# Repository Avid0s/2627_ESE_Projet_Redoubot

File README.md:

# 2627_ESE_PROJET_REDOUBOT

[Diagramme draw.io](https://app.diagrams.net/#G1vOe_3MKJzJUBpPdtP-GZ-P4Yg8ShrS2W#%7B%22pageId%22%3A%22ODYEVYFFD_o6EEWGu_Kz%22%7D)

[PDF MPU 6050](https://docs.google.com/document/d/1O3AgjvM2_tZX7ABNkbS3lNtyRqeFLNvJ6qVK9URJxNs/edit?usp=drive_link)

[BOM commande composants](https://docs.google.com/spreadsheets/d/1_k0gg7k1Y5h9V0FLCA0YabgreAiMSMoDTZmiZd1OaFM/edit?usp=sharing)

| Composant | Référence | Lien | Quantité |
|-----------|-----------|------|----------|
| STM32 | CPU_DS_stm32g431rb | [Datasheet](https://github.com/Avid0s/2627_ESE_Projet_Redoubot/blob/main/Datasheet/CPU_DS_stm32g431rb.pdf) | x1 |
| Drivers moteur | DRV8833 | [Datasheet](https://github.com/Avid0s/2627_ESE_Projet_Redoubot/blob/main/Datasheet/Drivers_drv8833.pdf) | x1 |
| Moteurs | FIT0483 | [Datasheet](https://github.com/Avid0s/2627_ESE_Projet_Redoubot/blob/main/Datasheet/Datasheet_moteur_FIT0483.pdf) | x2|
| Gyroscope/accelerometre | MPU6050 | [Datasheet](https://github.com/Avid0s/2627_ESE_Projet_Redoubot/blob/main/Datasheet/Gyro_MPU-6000_DATASHEET.pdf) | x1 |
| Servomotor | SER0039 | [Datasheet](https://github.com/Avid0s/2627_ESE_Projet_Redoubot/blob/main/Datasheet/Servo_SER0039.pdf) | x2 |
| TOF sensor | VL53LL0X | [Datasheet](https://github.com/Avid0s/2627_ESE_Projet_Redoubot/blob/main/Datasheet/TOF_vl53l0x.pdf) [Breakout Board](https://github.com/lfiack/ENSEA_VL53L0CXV0DH-1)| x1 |
| Capteur de couleur | Adafruit APDS9960 | [Datasheet](https://github.com/Avid0s/2627_ESE_Projet_Redoubot/blob/main/Datasheet/Capteur_Couleur_9075d4adc221e10b04bda232a5ca3905.pdf) | x1 |
| BMS | BQ25896RTWR | [Datasheet](https://github.com/Avid0s/2627_ESE_Projet_Redoubot/blob/main/Datasheet/BMS_bq25896.pdf) | x1 |  
| Batterie Lithium | XX | Fournie par ENSEA | x1 |
| Fuel Gauge | BQ27220YZFR | [Datasheet](https://www.ti.com/lit/ds/symlink/bq27220.pdf?ts=1790240333206&ref_url=https%253A%252F%252Fwww.mouser.fr%252F) | x1 |
| Sonde de programation | Conn_ST_STDC14 | Fournie par ENSEA| x1 |
| Lecteur MicroSD | Module MP3 DFPlayer | XX | x1 |
| Module Bluetooth | BT Module HM10 | XX | x1 |

La facon dont l'implémentation de fonctionnalités sera faite sera la suivante:

1 branche = 1 fonctionalité

Les branches seront nommées JMA/nom_de_la_fonctionnalitée pour une branche fonctionnalité de J. Mansard par exemple

Aucun push ne sera fait directement sur le main, tout sera merge post peer review

Cette methodologie vise à éviter les merge conflicts et simplifier l'assemblage des différents modules

## TODO :
- Timeline des tests phase bringup (tests réussis, échoués etc)
- faire un organigramme de la partie software pour arrêter de coder en blind
- Créer schémas de programmation, style de ce qui a été fait en cours de RTOS (session4 p7)
- Créer chronogrammes pour machines à état avec tâches blocantes

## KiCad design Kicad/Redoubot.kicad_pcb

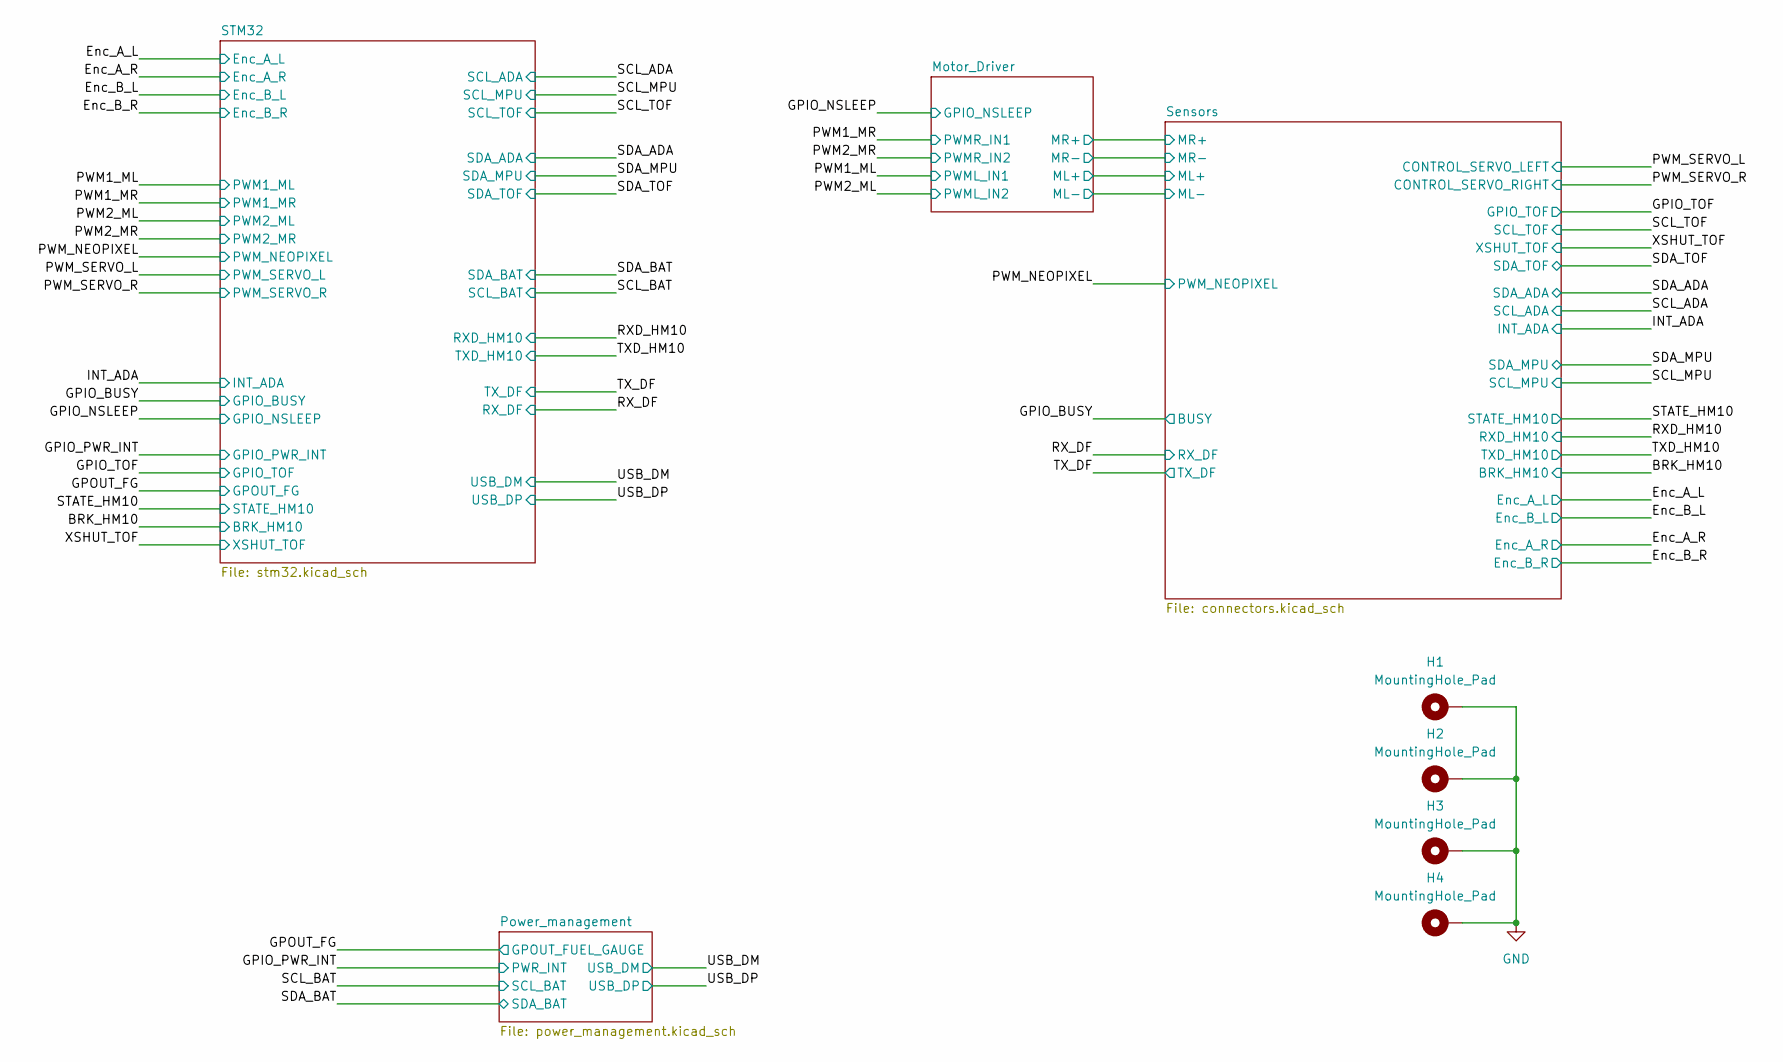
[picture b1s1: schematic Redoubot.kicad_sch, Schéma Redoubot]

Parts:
H1, H2, H3, H4: MountingHole_Pad; MountingHole_3.2mm_M3_ISO7380_Pad_TopBottom

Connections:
GND: H1.1 (1_1), H2.1 (1_1), H3.1 (1_1), H4.1 (1_1); also elsewhere on the board

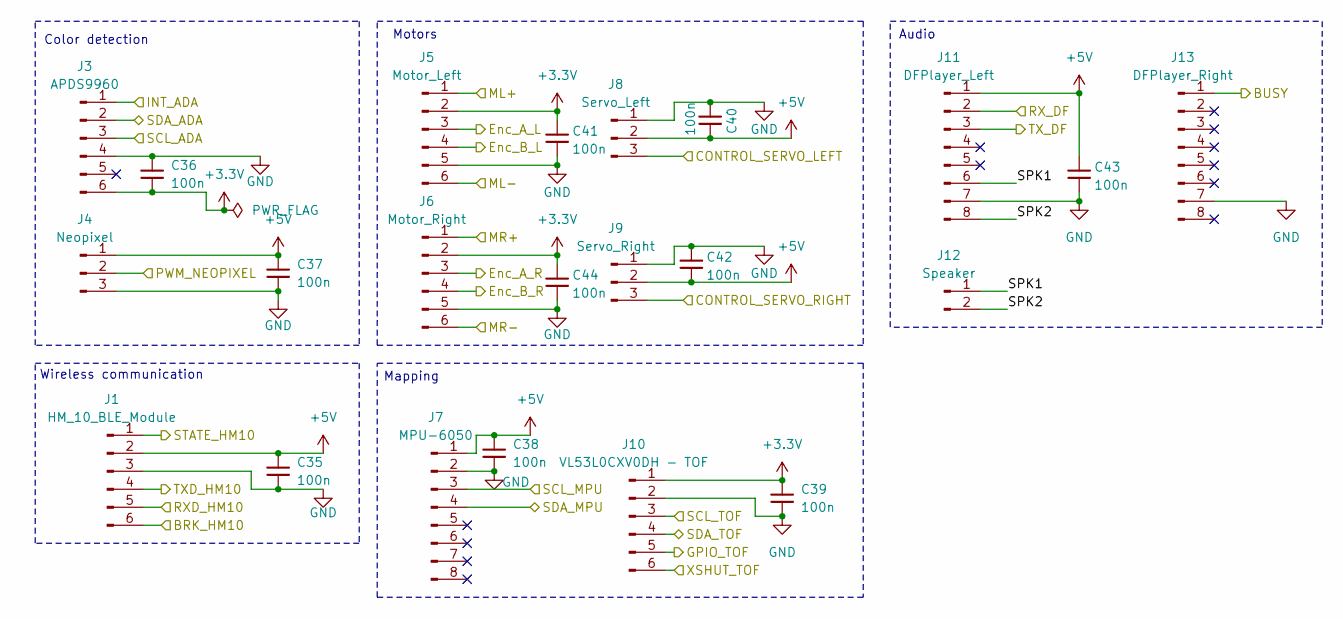
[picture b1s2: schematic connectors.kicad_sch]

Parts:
C35, C36, C37, C38, C39, C40, C41, C42, C43, C44: 100n; C_0402_1005Metric; JLCPCB Part # C1525
J1: HM_10_BLE_Module; JST_XH_B6B-XH-A_1x06_P2.50mm_Vertical
J3: APDS9960; JST_XH_B6B-XH-A_1x06_P2.50mm_Vertical
J4: Neopixel; JST_XH_B3B-XH-A_1x03_P2.50mm_Vertical
J5: Motor_Left; JST_XH_B6B-XH-A_1x06_P2.50mm_Vertical
J6: Motor_Right; JST_XH_B6B-XH-A_1x06_P2.50mm_Vertical
J7: MPU-6050; PinSocket_1x08_P2.54mm_Vertical; LCSC C24112
J8: Servo_Left; JST_XH_B3B-XH-A_1x03_P2.50mm_Vertical
J9: Servo_Right; JST_XH_B3B-XH-A_1x03_P2.50mm_Vertical
J10: VL53L0CXV0DH - TOF; JST_XH_B6B-XH-A_1x06_P2.50mm_Vertical; LCSC C91199
J11: DFPlayer_Left; PinSocket_1x08_P2.54mm_Vertical
J12: Speaker; JST_XH_B2B-XH-A_1x02_P2.50mm_Vertical
J13: DFPlayer_Right; PinSocket_1x08_P2.54mm_Vertical

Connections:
+3.3V: C36.2, C39.1, C41.1, C44.1, J3.6, J5.2, J6.2, J10.1; also elsewhere on the board
+5V: C35.1, C37.1, C38.1, C40.2, C42.2, C43.1, J1.2, J4.1, J7.1, J8.2, J9.2, J11.1; also elsewhere on the board
/BRK_HM10: J1.6; also elsewhere on the board
/Enc_A_L: J5.3; also elsewhere on the board
/Enc_A_R: J6.3; also elsewhere on the board
/Enc_B_L: J5.4; also elsewhere on the board
/Enc_B_R: J6.4; also elsewhere on the board
/GPIO_BUSY: J13.1; also elsewhere on the board
/GPIO_TOF: J10.5; also elsewhere on the board
/INT_ADA: J3.1; also elsewhere on the board
/Motor_Driver/ML+: J5.1; also elsewhere on the board
/Motor_Driver/ML-: J5.6; also elsewhere on the board
/Motor_Driver/MR+: J6.1; also elsewhere on the board
/Motor_Driver/MR-: J6.6; also elsewhere on the board
/PWM_NEOPIXEL: J4.2; also elsewhere on the board
/PWM_SERVO_L: J8.3; also elsewhere on the board
/PWM_SERVO_R: J9.3; also elsewhere on the board
/RXD_HM10: J1.5; also elsewhere on the board
/RX_DF: J11.2; also elsewhere on the board
/SCL_ADA: J3.3, J7.3, J10.3; also elsewhere on the board
/SDA_ADA: J3.2, J7.4, J10.4; also elsewhere on the board
/STATE_HM10: J1.1; also elsewhere on the board
/Sensors/SPK1: J11.6, J12.1
/Sensors/SPK2: J11.8, J12.2
/TXD_HM10: J1.4; also elsewhere on the board
/TX_DF: J11.3; also elsewhere on the board
/XSHUT_TOF: J10.6; also elsewhere on the board
GND: C35.2, C36.1, C37.2, C38.2, C39.2, C40.1, C41.2, C42.1, C43.2, C44.2, J1.3, J3.4, J4.3, J5.5, J6.5, J7.2, J8.1, J9.1, J10.2, J11.7, J13.7; also elsewhere on the board

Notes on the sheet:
Motors
Wireless communication
Color detection
Mapping
Audio

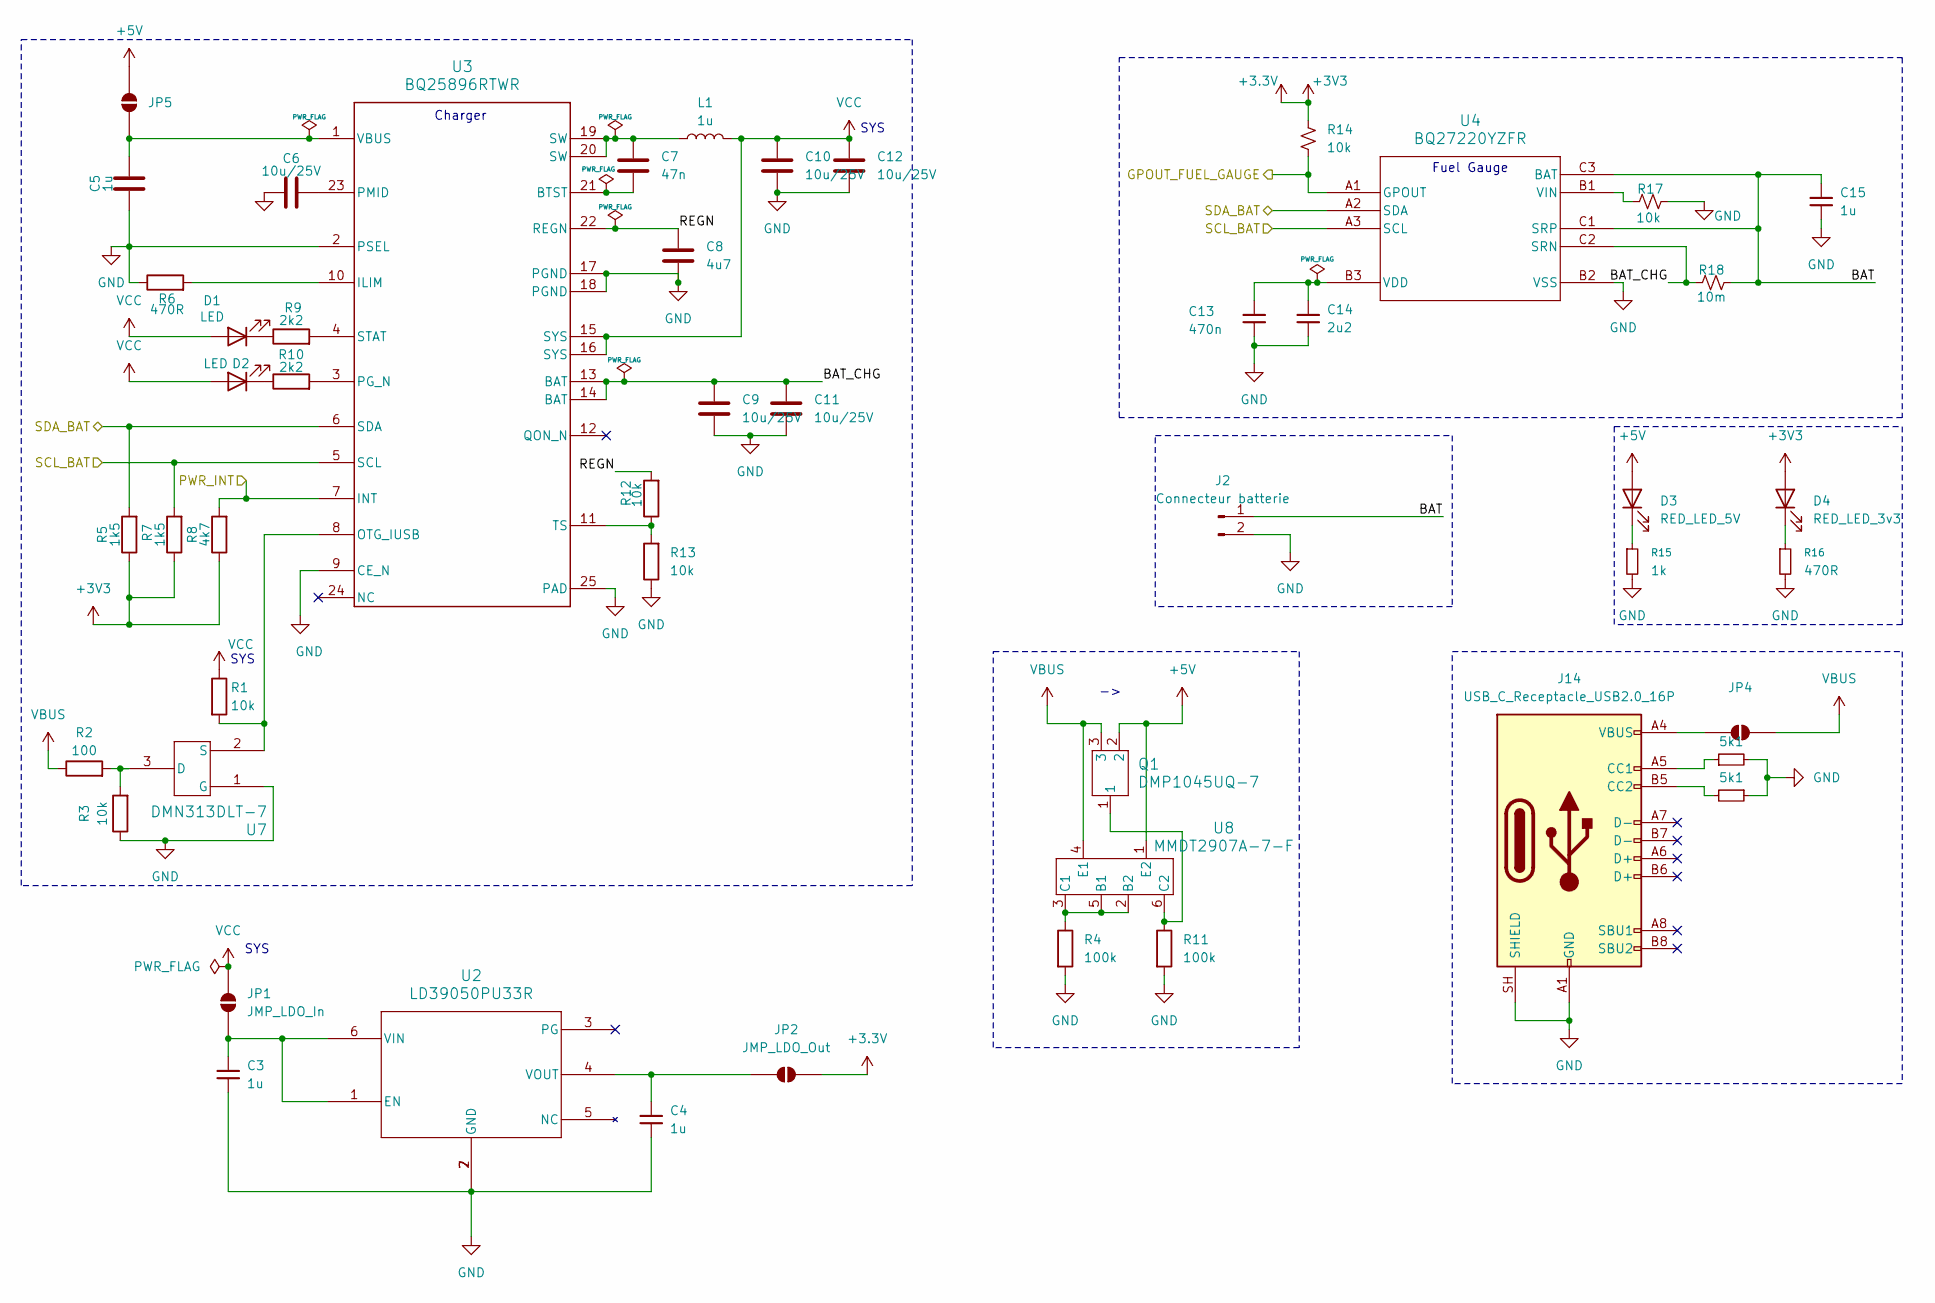
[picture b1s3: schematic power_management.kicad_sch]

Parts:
C3, C4, C5, C15: 1u; C_0402_1005Metric; JLCPCB Part # C52923
C6, C9, C10, C11, C12: 10u/25V; C_0603_1608Metric; JLCPCB Part # C96446
C7: 47n; C_0603_1608Metric; JLCPCB Part # C1622
C8: 4u7; C_0402_1005Metric; JLCPCB Part # C23733
C13: 470n; C_0603_1608Metric; JLCPCB Part # C1623
C14: 2u2; C_0402_1005Metric; JLCPCB Part # C12530
D1, D2: LED; LED_0603_1608Metric; JLCPCB Part # C965804
D3: RED_LED_5V; LED_0603_1608Metric; JLCPCB Part # C965804
D4: RED_LED_3v3; LED_0603_1608Metric; JLCPCB Part # C965804
J2: Connecteur batterie; JST_XH_B2B-XH-A_1x02_P2.50mm_Vertical
J14: USB_C_Receptacle_USB2.0_16P; USB_C_Receptacle_GCT_USB4105-xx-A_16P_TopMnt_Horizontal
JP1: JMP_LDO_In; SolderJumper-2_P1.3mm_Open_TrianglePad1.0x1.5mm
JP2: JMP_LDO_Out; SolderJumper-2_P1.3mm_Open_TrianglePad1.0x1.5mm
JP4, JP5: JMP_Battery; SolderJumper-2_P1.3mm_Open_TrianglePad1.0x1.5mm
L1: 1u; L_Sunlord_SWPA4030S; JLCPCB Part # C42193
Q1: DMP1045UQ-7; DMP1045UQ-7_DIO; JLCPCB Part # C706746
R1, R3, R12, R13, R14, R17: 10k; R_0402_1005Metric; JLCPCB Part # C25744
R2: 100; R_0402_1005Metric; JLCPCB Part # C25076
R4, R11: 100k; R_0402_1005Metric; JLCPCB Part # C25741
R5, R7: 1k5; R_0402_1005Metric; JLCPCB Part # C25867
R6, R16: 470R; R_0402_1005Metric; JLCPCB Part # C25117
R8: 4k7; R_0402_1005Metric; JLCPCB Part # C25900
R9, R10: 2k2; R_0402_1005Metric; JLCPCB Part # C25879
R15: 1k; R_0402_1005Metric; JLCPCB Part # C11702
R18: 10m; R_1206_3216Metric; JLCPCB Part # C105362
R20, R21: 5k1; R_0402_1005Metric; JLCPCB Part # C25905
U2: LD39050PU33R; DFN6_3X3_STM; JLCPCB Part # C132827
U3: BQ25896RTWR; RTW0024H; LCSC C181475
U4: BQ27220YZFR; BGA-9_1.6x1.6mm_Layout3x3_P0.5mm; LCSC C528617
U7: DMN313DLT-7; SOT-523_DIO; JLCPCB Part # C155524
U8: MMDT2907A-7-F; SOT-363_DIO; JLCPCB Part # C460232

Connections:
+3.3V: D4.2 (A), JP2.2 (B), R5.1, R7.1, R8.1, R14.1; also elsewhere on the board
+5V: D3.2 (A), JP5.2 (B), Q1.2, U8.1 (E2); also elsewhere on the board
/GPIO_PWR_INT: R8.2, U3.7 (INT); also elsewhere on the board
/GPOUT_FG: R14.2, U4.A1 (GPOUT); also elsewhere on the board
/Power_management/BAT: C15.1, J2.1, R18.2, U4.C1 (SRP), U4.C3 (BAT)
/Power_management/BAT_CHG: C9.2, C11.2, R18.1, U3.13 (BAT), U3.14 (BAT), U4.C2 (SRN)
/Power_management/REGN: C8.2, R12.2, U3.22 (REGN)
/SCL_BAT: R7.2, U3.5 (SCL), U4.A3 (SCL); also elsewhere on the board
/SDA_BAT: R5.2, U3.6 (SDA), U4.A2 (SDA); also elsewhere on the board
GND: C3.1, C4.2, C5.1, C6.1, C8.1, C9.1, C10.1, C11.1, C12.1, C13.2, C14.2, C15.2, J2.2, J14.A1 (GND), J14.A12 (GND), J14.B1 (GND), J14.B12 (GND), J14.SH (SHIELD), R3.1, R4.2, R6.1, R11.2, R13.1, R15.2, R16.2, R17.1, R20.2, R21.1, U2.2 (GND), U2.7 (GND), U3.2 (PSEL), U3.9 (CE_N), U3.17 (PGND), U3.18 (PGND), U3.25 (PAD), U4.B2 (VSS), U7.1 (G); also elsewhere on the board
unnamed: C7.2, L1.1, U3.19 (SW), U3.20 (SW)
unnamed: D1.1 (K), R9.1
unnamed: D2.1 (K), R10.1
unnamed: D3.1 (K), R15.1
unnamed: D4.1 (K), R16.1
unnamed: J14.A5 (CC1), R20.1
unnamed: J14.B5 (CC2), R21.2
unnamed: C3.2, JP1.1 (A), U2.1 (EN), U2.6 (VIN)
unnamed: C4.1, JP2.1 (A), U2.4 (VOUT)
unnamed: J14.A4 (VBUS), J14.A9 (VBUS), J14.B4 (VBUS), J14.B9 (VBUS), JP4.1 (A)
unnamed: C5.2, JP5.1 (A), U3.1 (VBUS)
unnamed: C7.1, U3.21 (BTST)
unnamed: R6.2, U3.10 (ILIM)
unnamed: R1.2, U3.8 (OTG_IUSB), U7.2 (S)
unnamed: R10.2, U3.3 (PG_N)
unnamed: C6.2, U3.23 (PMID)
unnamed: R9.2, U3.4 (STAT)
unnamed: R12.1, R13.2, U3.11 (TS)
unnamed: C13.1, C14.1, U4.B3 (VDD)
unnamed: R17.2, U4.B1 (VIN)
unnamed: R2.2, R3.2, U7.3 (D)
unnamed: R4.1, U8.2 (B2), U8.3 (C1), U8.5 (B1)
unnamed: Q1.1, R11.1, U8.6 (C2)
VBUS: JP4.2 (B), Q1.3, R2.1, U8.4 (E1)
VCC: C10.2, C12.2, D1.2 (A), D2.2 (A), JP1.2 (B), L1.2, R1.1, U3.15 (SYS), U3.16 (SYS)

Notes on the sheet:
SYS
Fuel Gauge
Charger

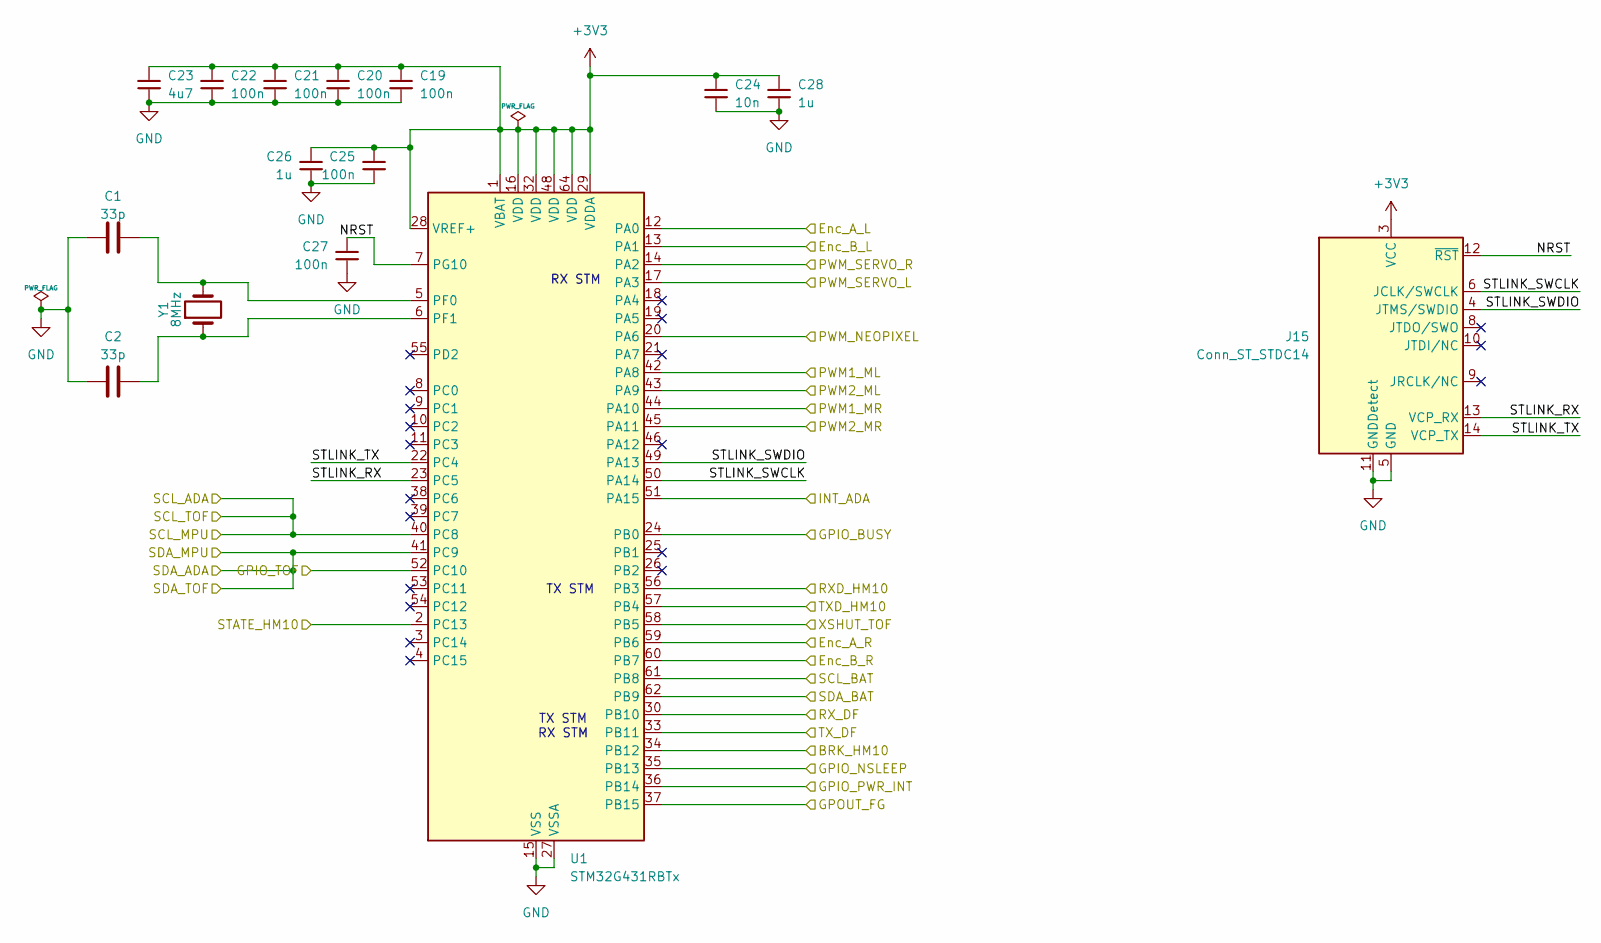
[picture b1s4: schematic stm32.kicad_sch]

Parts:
C1, C2: 33p; C_0402_1005Metric; JLCPCB Part # C1562
C19, C20, C21, C22, C25, C27: 100n; C_0402_1005Metric; JLCPCB Part # C1525
C23: 4u7; C_0402_1005Metric; JLCPCB Part # C23733
C24: 10n; C_0402_1005Metric; JLCPCB Part # C15195
C26, C28: 1u; C_0402_1005Metric; JLCPCB Part # C52923
J15: Conn_ST_STDC14; PinHeader_2x07_P1.27mm_Vertical_SMD
U1: STM32G431RBTx; LQFP-64_10x10mm_P0.5mm; LCSC C431633
Y1: 8MHz; Crystal_SMD_HC49-SD; JLCPCB Part # C115962

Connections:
+3.3V: C19.1, C20.1, C21.1, C22.1, C23.1, C24.1, C25.1, C26.1, C28.1, J15.3 (VCC), U1.1 (VBAT), U1.16 (VDD), U1.28 (VREF+), U1.29 (VDDA), U1.32 (VDD), U1.48 (VDD), U1.64 (VDD); also elsewhere on the board
/BRK_HM10: U1.34 (PB12); also elsewhere on the board
/Enc_A_L: U1.12 (PA0); also elsewhere on the board
/Enc_A_R: U1.59 (PB6); also elsewhere on the board
/Enc_B_L: U1.13 (PA1); also elsewhere on the board
/Enc_B_R: U1.60 (PB7); also elsewhere on the board
/GPIO_BUSY: U1.24 (PB0); also elsewhere on the board
/GPIO_NSLEEP: U1.35 (PB13); also elsewhere on the board
/GPIO_PWR_INT: U1.36 (PB14); also elsewhere on the board
/GPIO_TOF: U1.52 (PC10); also elsewhere on the board
/GPOUT_FG: U1.37 (PB15); also elsewhere on the board
/INT_ADA: U1.51 (PA15); also elsewhere on the board
/PWM1_ML: U1.42 (PA8); also elsewhere on the board
/PWM1_MR: U1.44 (PA10); also elsewhere on the board
/PWM2_ML: U1.43 (PA9); also elsewhere on the board
/PWM2_MR: U1.45 (PA11); also elsewhere on the board
/PWM_NEOPIXEL: U1.20 (PA6); also elsewhere on the board
/PWM_SERVO_L: U1.17 (PA3); also elsewhere on the board
/PWM_SERVO_R: U1.14 (PA2); also elsewhere on the board
/RXD_HM10: U1.56 (PB3); also elsewhere on the board
/RX_DF: U1.30 (PB10); also elsewhere on the board
/SCL_ADA: U1.40 (PC8); also elsewhere on the board
/SCL_BAT: U1.61 (PB8); also elsewhere on the board
/SDA_ADA: U1.41 (PC9); also elsewhere on the board
/SDA_BAT: U1.62 (PB9); also elsewhere on the board
/STATE_HM10: U1.2 (PC13); also elsewhere on the board
/STM32/NRST: C27.1, J15.12 (~RST), U1.7 (PG10)
/STM32/STLINK_RX: J15.13 (VCP_RX), U1.23 (PC5)
/STM32/STLINK_SWCLK: J15.6 (JCLK/SWCLK), U1.50 (PA14)
/STM32/STLINK_SWDIO: J15.4 (JTMS/SWDIO), U1.49 (PA13)
/STM32/STLINK_TX: J15.14 (VCP_TX), U1.22 (PC4)
/TXD_HM10: U1.57 (PB4); also elsewhere on the board
/TX_DF: U1.33 (PB11); also elsewhere on the board
/XSHUT_TOF: U1.58 (PB5); also elsewhere on the board
GND: C1.1, C2.1, C19.2, C20.2, C21.2, C22.2, C23.2, C24.2, C25.2, C26.2, C27.2, C28.2, J15.5 (GND), J15.7 (GND), J15.11 (GNDDetect), U1.15 (VSS), U1.27 (VSSA), U1.31 (VSS), U1.47 (VSS), U1.63 (VSS); also elsewhere on the board
unnamed: C1.2, U1.5 (PF0), Y1.2
unnamed: C2.2, U1.6 (PF1), Y1.1

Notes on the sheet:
RX STM
TX STM RX STM
TX STM

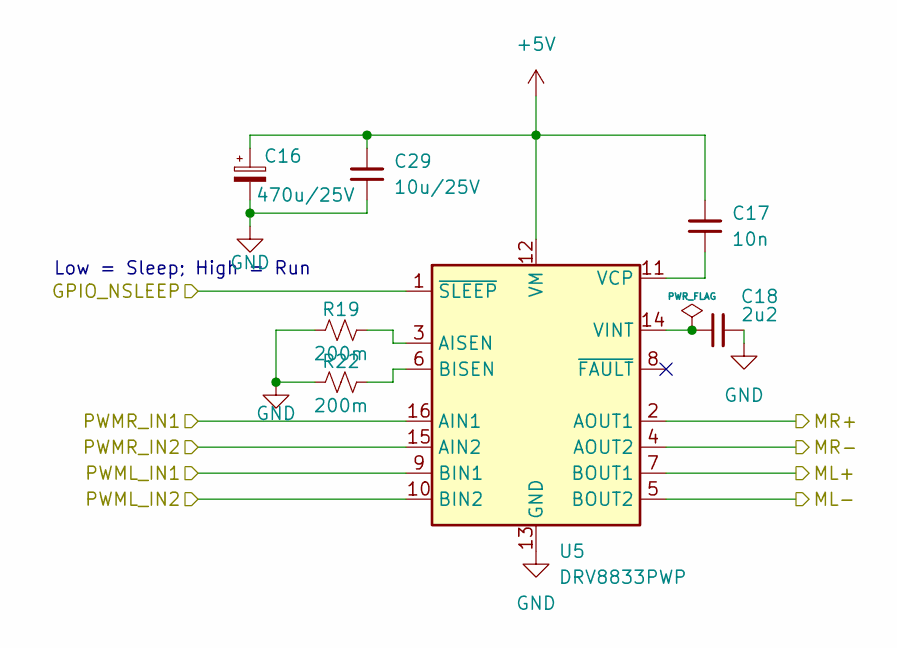
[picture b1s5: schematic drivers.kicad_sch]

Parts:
C16: 470u/25V; CP_Elec_8x10.5; JLCPCB Part # C48935394
C17: 10n; C_0402_1005Metric; JLCPCB Part # C15195
C18: 2u2; C_0402_1005Metric; JLCPCB Part # C12530
C29: 10u/25V; C_0603_1608Metric; JLCPCB Part # C96446
R19, R22: 200m; R_1206_3216Metric; JLCPCB Part # C160920
U5: DRV8833PWP; HTSSOP-16-1EP_4.4x5mm_P0.65mm_EP3.4x5mm_Mask2.46x2.31mm_The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; LCSC C50506

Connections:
+5V: C16.1, C17.1, C29.1, U5.12 (VM); also elsewhere on the board
/GPIO_NSLEEP: U5.1 (~SLEEP); also elsewhere on the board
/Motor_Driver/ML+: U5.7 (BOUT1); also elsewhere on the board
/Motor_Driver/ML-: U5.5 (BOUT2); also elsewhere on the board
/Motor_Driver/MR+: U5.2 (AOUT1); also elsewhere on the board
/Motor_Driver/MR-: U5.4 (AOUT2); also elsewhere on the board
/PWM1_ML: U5.9 (BIN1); also elsewhere on the board
/PWM1_MR: U5.16 (AIN1); also elsewhere on the board
/PWM2_ML: U5.10 (BIN2); also elsewhere on the board
/PWM2_MR: U5.15 (AIN2); also elsewhere on the board
GND: C16.2, C18.2, C29.2, R19.1, R22.1, U5.13 (GND), U5.17 (GND); also elsewhere on the board
unnamed: R19.2, U5.3 (AISEN)
unnamed: R22.2, U5.6 (BISEN)
unnamed: C17.2, U5.11 (VCP)
unnamed: C18.1, U5.14 (VINT)

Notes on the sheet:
Low = Sleep; High = Run

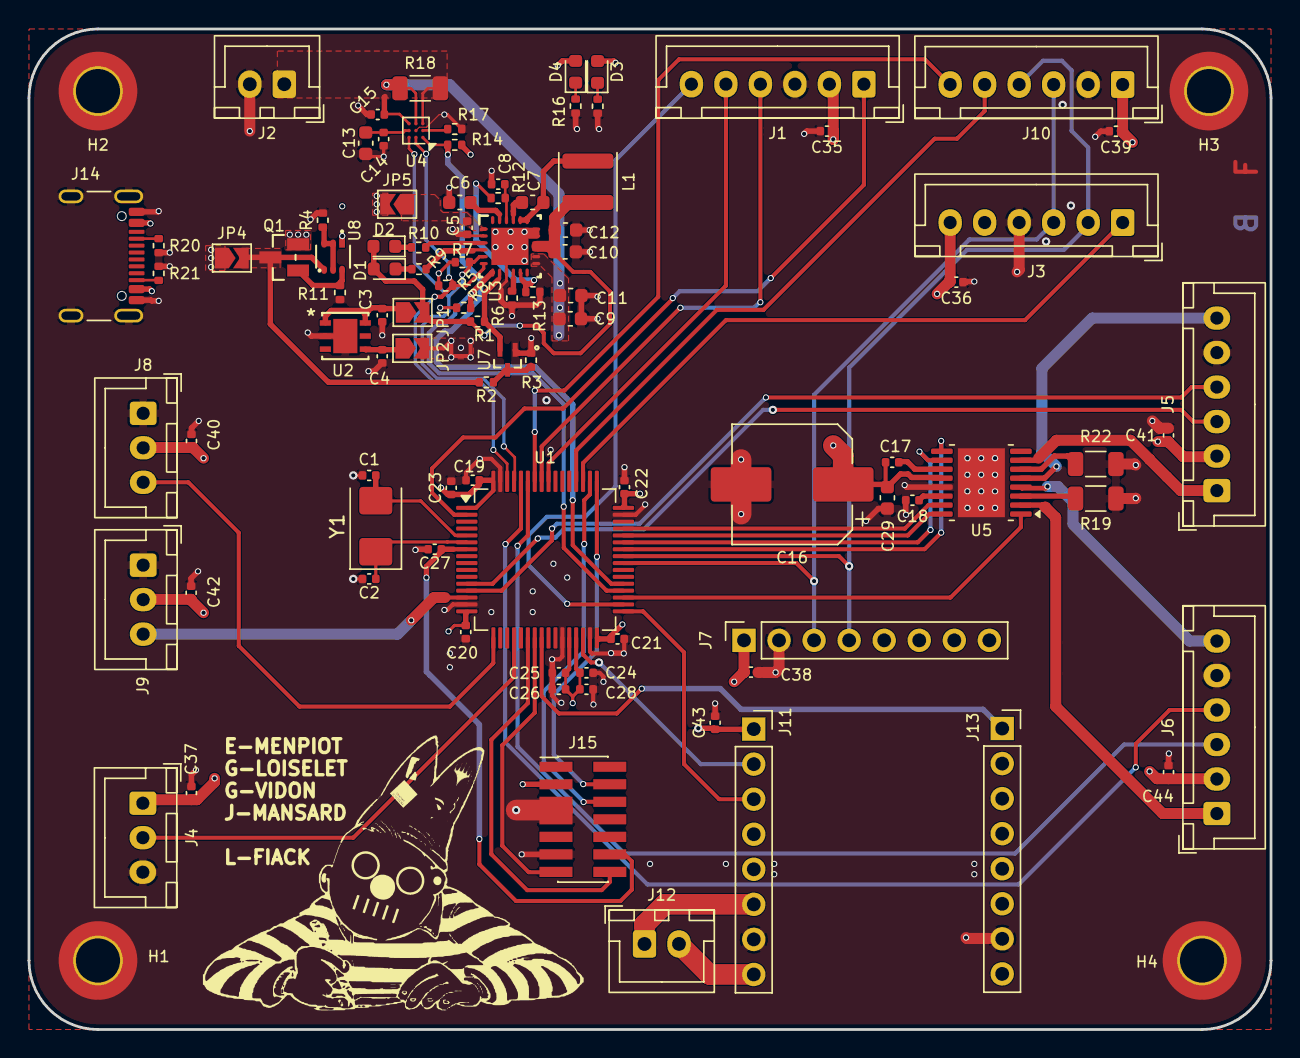
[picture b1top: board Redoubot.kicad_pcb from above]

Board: 4 copper layers, 90.0 x 72.5 mm, 98 parts (0 on the bottom side), 76 nets.

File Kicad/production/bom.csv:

Designator,Footprint,Quantity,Value,LCSC Part #
"C1, C2",0402,2,33p,C1562 
"C10, C11, C12, C29, C6, C9",0603,6,10u/25V,C96446
C13,0603,1,470n,C1623
"C14, C18",0402,2,2u2,C12530
"C15, C26, C28, C3, C4, C5",0402,6,1u,C52923
C16,CP_Elec_8x10.5,1,470u/25V,C48935394
"C17, C24",0402,2,10n,C15195
"C19, C20, C21, C22, C25, C27, C35, C36, C37, C38, C39, C40, C41, C42, C43, C44",0402,16,100n,C1525
"C23, C8",0402,2,4u7,C23733
C7,0603,1,47n,C1622
"D1, D2",0603,2,LED,C965804
D3,0603,1,RED_LED_5V,C965804
D4,0603,1,RED_LED_3v3,C965804
J1,JST_XH_B6B-XH-A_1x06_P2.50mm_Vertical,1,HM_10_BLE_Module,
J10,JST_XH_B6B-XH-A_1x06_P2.50mm_Vertical,1,VL53L0CXV0DH - TOF,C91199
J11,PinSocket_1x08_P2.54mm_Vertical,1,DFPlayer_Left,
J12,JST_XH_B2B-XH-A_1x02_P2.50mm_Vertical,1,Speaker,
J13,PinSocket_1x08_P2.54mm_Vertical,1,DFPlayer_Right,
J14,USB_C_Receptacle_GCT_USB4105-xx-A_16P_TopMnt_Horizontal,1,USB_C_Receptacle_USB2.0_16P,
J15,PinHeader_2x07_P1.27mm_Vertical_SMD,1,Conn_ST_STDC14,
J2,JST_XH_B2B-XH-A_1x02_P2.50mm_Vertical,1,Connecteur batterie,
J3,JST_XH_B6B-XH-A_1x06_P2.50mm_Vertical,1,APDS9960,
J4,JST_XH_B3B-XH-A_1x03_P2.50mm_Vertical,1,Neopixel,
J5,JST_XH_B6B-XH-A_1x06_P2.50mm_Vertical,1,Motor_Left,
J6,JST_XH_B6B-XH-A_1x06_P2.50mm_Vertical,1,Motor_Right,
J7,PinSocket_1x08_P2.54mm_Vertical,1,MPU-6050,C24112
J8,JST_XH_B3B-XH-A_1x03_P2.50mm_Vertical,1,Servo_Left,
J9,JST_XH_B3B-XH-A_1x03_P2.50mm_Vertical,1,Servo_Right,
L1,L_Sunlord_SWPA4030S,1,1u,C42193
Q1,DMP1045UQ-7_DIO,1,DMP1045UQ-7,C706746
"R1, R12, R13, R14, R17, R3",0402,6,10k,C25744
"R10, R9",0402,2,2k2,C25879
"R11, R4",0402,2,100k,C25741
R15,0402,1,1k,C11702
"R16, R6",0402,2,470R,C25117
R18,1206,1,10m,C105362
"R19, R22",1206,2,200m,C160920
R2,0402,1,100,C25076
"R20, R21",0402,2,5k1,C25905
"R5, R7",0402,2,1k5,C25867
R8,0402,1,4k7,C25900
U1,LQFP-64_10x10mm_P0.5mm,1,STM32G431RBTx,C431633
U2,DFN6_3X3_STM,1,LD39050PU33R,C132827
U3,RTW0024H,1,BQ25896RTWR,C181475
U4,BGA-9_1.6x1.6mm_Layout3x3_P0.5mm,1,BQ27220YZFR,C528617
U5,HTSSOP-16-1EP_4.4x5mm_P0.65mm_EP3.4x5mm_Mask2.46x2.31mm_ThermalVias,1,DRV8833PWP,C50506
U7,SOT-523_DIO,1,DMN313DLT-7,C155524
U8,SOT-363_DIO,1,MMDT2907A-7-F,C460232
Y1,Crystal_SMD_5032-2Pin_5.0x3.2mm,1,8MHz,C115962

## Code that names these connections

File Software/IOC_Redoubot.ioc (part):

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Mcu.Name=STM32G431R(6-8-B)Tx
Mcu.Package=LQFP64
Mcu.UserName=STM32G431RBTx
PA0.GPIOParameters=GPIO_Label
PA0.GPIO_Label=ENCODER1A
PA0.Signal=S_TIM2_CH1
PA1.GPIOParameters=GPIO_Label
PA1.GPIO_Label=ENCODER1B
PA1.Signal=S_TIM2_CH2
PA10.GPIOParameters=GPIO_Label
PA10.GPIO_Label=PWM1_MR
PA10.Signal=S_TIM1_CH3
PA11.GPIOParameters=GPIO_Label
PA11.GPIO_Label=PWM2_MR
PA11.Signal=S_TIM1_CH4
PA13.Mode=Serial_Wire
PA13.Signal=SYS_JTMS-SWDIO
PA14.Mode=Serial_Wire
PA14.Signal=SYS_JTCK-SWCLK
PA15.GPIOParameters=GPIO_Label
PA15.GPIO_Label=INT_ADA
PA15.Signal=GPIO_Output
PA2.GPIOParameters=GPIO_Label
PA2.GPIO_Label=SERVOR
PA2.Signal=S_TIM15_CH1
PA3.GPIOParameters=GPIO_Label
PA3.GPIO_Label=SERVOL
PA3.Signal=S_TIM15_CH2
PA6.GPIOParameters=GPIO_Label
PA6.GPIO_Label=PWM_NEOPIXEL
PA6.Signal=S_TIM3_CH1
PA8.GPIOParameters=GPIO_Label
PA8.GPIO_Label=PWM1_ML
PA8.Signal=S_TIM1_CH1
PA9.GPIOParameters=GPIO_Label
PA9.GPIO_Label=PWM2_ML
PA9.Signal=S_TIM1_CH2
PB0.GPIOParameters=GPIO_Label
PB0.GPIO_Label=GPIO_BUSY
PB0.Signal=GPIO_Input
PB10.GPIOParameters=GPIO_Label
PB10.GPIO_Label=RX_DF
PB10.Mode=Asynchronous
PB10.Signal=USART3_TX
PB11.GPIOParameters=GPIO_Label
PB11.GPIO_Label=TX_DF
PB11.Mode=Asynchronous
PB11.Signal=USART3_RX
PB12.GPIOParameters=GPIO_Label
PB12.GPIO_Label=BRK_HM10
PB12.Signal=GPIO_Output
PB13.GPIOParameters=GPIO_Label
PB13.GPIO_Label=GPIO_NSLEEP
PB13.Signal=GPIO_Output
PB14.GPIOParameters=GPIO_Label
PB14.GPIO_Label=GPIO_PWR_INT
PB14.Signal=GPIO_Input
PB15.GPIOParameters=GPIO_Label
PB15.GPIO_Label=GPOUT_FG
PB15.Signal=GPIO_Input
PB3.GPIOParameters=GPIO_Label
PB3.GPIO_Label=RXD_HM10
PB3.Mode=Asynchronous
PB3.Signal=USART2_TX
PB4.GPIOParameters=GPIO_Label
PB4.GPIO_Label=TXD_HM10
PB4.Mode=Asynchronous
PB4.Signal=USART2_RX
PB5.GPIOParameters=GPIO_PuPd,GPIO_Label,GPIO_ModeDefaultOutputPP
PB5.GPIO_Label=XSHUT_TOF
PB5.GPIO_ModeDefaultOutputPP=GPIO_MODE_OUTPUT_OD
PB5.GPIO_PuPd=GPIO_NOPULL
PB5.Signal=GPIO_Output
PB6.GPIOParameters=GPIO_Label
PB6.GPIO_Label=ENCODER2A
PB6.Signal=S_TIM4_CH1
PB7.GPIOParameters=GPIO_Label
PB7.GPIO_Label=ENCODER2B
PB7.Signal=S_TIM4_CH2
PB8-BOOT0.Mode=I2C
PB8-BOOT0.Signal=I2C1_SCL
PB9.Mode=I2C
PB9.Signal=I2C1_SDA
PC10.GPIOParameters=GPIO_PuPd,GPIO_Label
PC10.GPIO_Label=GPIO_TOF
PC10.GPIO_PuPd=GPIO_PULLUP
PC10.Signal=GPIO_Input
PC13.GPIOParameters=GPIO_Label
PC13.GPIO_Label=STATE_HM10
PC13.Signal=GPIO_Input
PC4.GPIOParameters=GPIO_Label
PC4.GPIO_Label=STLINK_TX
PC4.Mode=Asynchronous
PC4.Signal=USART1_TX
PC5.GPIOParameters=GPIO_Label
PC5.GPIO_Label=STLINK_RX
PC5.Mode=Asynchronous
PC5.Signal=USART1_RX
PC8.GPIOParameters=GPIO_Label
PC8.GPIO_Label=SCL_MPU_TOF_ADA
PC8.Mode=I2C
PC8.Signal=I2C3_SCL
PC9.GPIOParameters=GPIO_Label
PC9.GPIO_Label=SDA_MPU_TOF_ADA
PC9.Mode=I2C
PC9.Signal=I2C3_SDA
PD2.GPIOParameters=GPIO_Label
PD2.GPIO_Label=GPIO_OTG_EN
PD2.Signal=GPIO_Output
PF0-OSC_IN.Mode=HSE-External-Oscillator
PF0-OSC_IN.Signal=RCC_OSC_IN
PF1-OSC_OUT.Mode=HSE-External-Oscillator
PF1-OSC_OUT.Signal=RCC_OSC_OUT
RCC.HSE_VALUE=8000000
RCC.SYSCLKFreq_VALUE=170000000
RCC.SYSCLKSource=RCC_SYSCLKSOURCE_PLLCLK
board=custom

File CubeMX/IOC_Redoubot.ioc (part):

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Mcu.Name=STM32G431R(6-8-B)Tx
Mcu.Package=LQFP64
Mcu.UserName=STM32G431RBTx
PA0.GPIOParameters=GPIO_Label
PA0.GPIO_Label=PWM_SERVO_R
PA0.Signal=S_TIM2_CH1
PA1.GPIOParameters=GPIO_Label
PA1.GPIO_Label=PWM_SERVO_L
PA1.Signal=S_TIM2_CH2
PA11.Mode=Device
PA11.Signal=USB_DM
PA12.Mode=Device
PA12.Signal=USB_DP
PA13.Mode=I2C
PA13.Signal=I2C1_SCL
PA14.Mode=I2C
PA14.Signal=I2C1_SDA
PA2.GPIOParameters=GPIO_Label
PA2.GPIO_Label=RXD_HM10
PA2.Mode=Asynchronous
PA2.Signal=USART2_TX
PA3.GPIOParameters=GPIO_Label
PA3.GPIO_Label=TXD_HM10
PA3.Mode=Asynchronous
PA3.Signal=USART2_RX
PA6.GPIOParameters=GPIO_Label
PA6.GPIO_Label=PWM_NEOPIXEL
PA6.Signal=S_TIM3_CH1
PA9.GPIOParameters=GPIO_Label
PA9.GPIO_Label=INT_ADA
PA9.Signal=GPIO_Output
PB0.GPIOParameters=GPIO_Label
PB0.GPIO_Label=GPIO_BUSY
PB0.Signal=GPIO_Input
PB10.GPIOParameters=GPIO_Label
PB10.GPIO_Label=RX_DF
PB10.Mode=Asynchronous
PB10.Signal=USART3_TX
PB11.GPIOParameters=GPIO_Label
PB11.GPIO_Label=TX_DF
PB11.Mode=Asynchronous
PB11.Signal=USART3_RX
PB12.GPIOParameters=GPIO_Label
PB12.GPIO_Label=BRK_HM10
PB12.Signal=GPIO_Output
PB13.GPIOParameters=GPIO_Label
PB13.GPIO_Label=GPIO_NSLEEP
PB13.Signal=GPIO_Output
PB14.GPIOParameters=GPIO_Label
PB14.GPIO_Label=GPIO_PWR_INT
PB14.Signal=GPIO_Input
PB15.GPIOParameters=GPIO_Label
PB15.GPIO_Label=GPOUT_FG
PB15.Signal=GPIO_Input
PB4.GPIOParameters=GPIO_Label
PB4.GPIO_Label=GPIO_OTG_EN
PB4.Signal=GPIO_Output
PB5.GPIOParameters=GPIO_Label
PB5.GPIO_Label=XSHUT_TOF
PB5.Signal=GPIO_Output
PB6.GPIOParameters=GPIO_Label
PB6.GPIO_Label=GPIO_TOF
PB6.Signal=GPIO_Input
PB9.GPIOParameters=GPIO_Label
PB9.GPIO_Label=STATE_HM10
PB9.Signal=GPIO_Input
PC0.GPIOParameters=GPIO_Label
PC0.GPIO_Label=PWM1_ML
PC0.Signal=S_TIM1_CH1
PC1.GPIOParameters=GPIO_Label
PC1.GPIO_Label=PWM2_ML
PC1.Signal=S_TIM1_CH2
PC2.GPIOParameters=GPIO_Label
PC2.GPIO_Label=PWM1_MR
PC2.Signal=S_TIM1_CH3
PC3.GPIOParameters=GPIO_Label
PC3.GPIO_Label=PWM2_MR
PC3.Signal=S_TIM1_CH4
PC8.GPIOParameters=GPIO_Label
PC8.GPIO_Label=SCL_MPU
PC8.Mode=I2C
PC8.Signal=I2C3_SCL
PC9.GPIOParameters=GPIO_Label
PC9.GPIO_Label=SDA_MPU
PC9.Mode=I2C
PC9.Signal=I2C3_SDA
PF0-OSC_IN.GPIOParameters=GPIO_Label
PF0-OSC_IN.GPIO_Label=Quartz_0
PF0-OSC_IN.Signal=GPIO_Input
PF1-OSC_OUT.GPIOParameters=GPIO_Label
PF1-OSC_OUT.GPIO_Label=Quartz_1
PF1-OSC_OUT.Signal=GPIO_Input
RCC.HSE_VALUE=8000000
RCC.SYSCLKFreq_VALUE=16000000
board=custom
